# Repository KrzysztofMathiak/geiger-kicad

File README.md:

# geiger-kicad
This repository contains a NODEMCU-ESP32 based geiger counter.
It contains full pcb schematics and code required to run by hosting a web server on the ESP board.

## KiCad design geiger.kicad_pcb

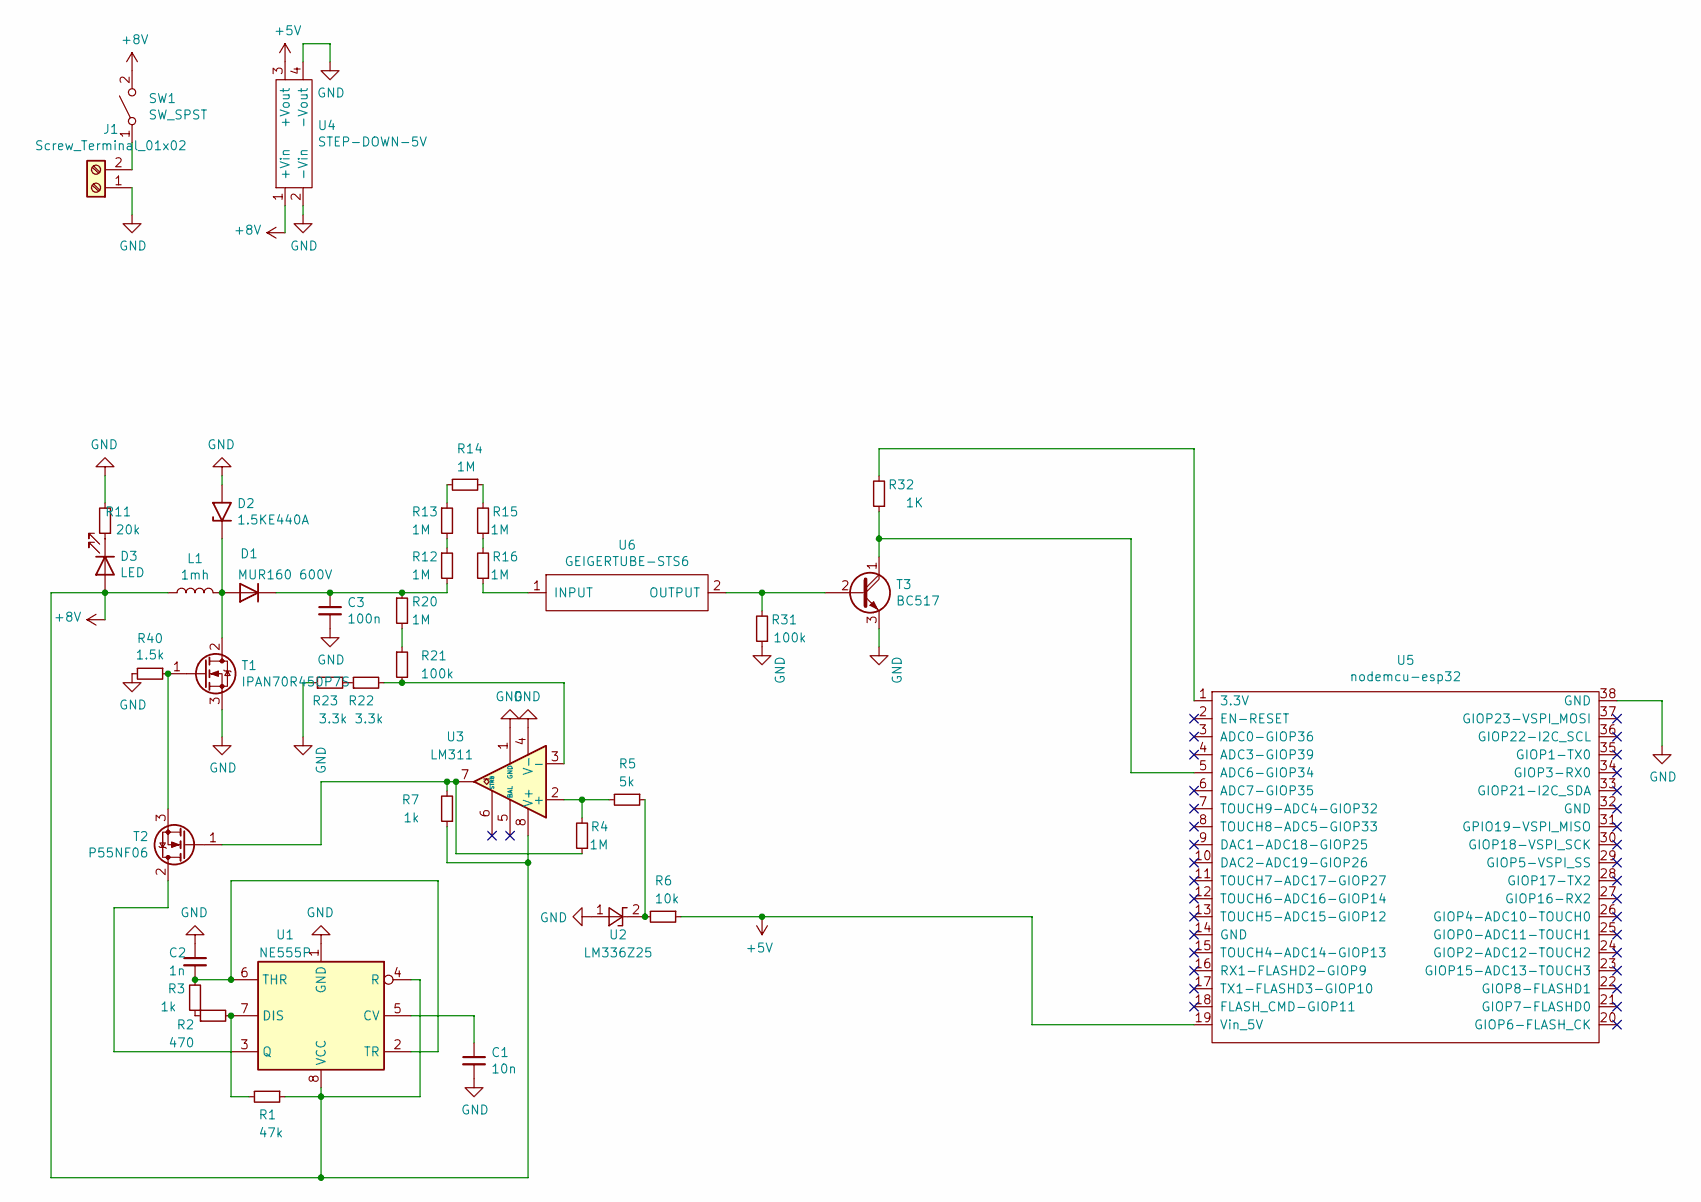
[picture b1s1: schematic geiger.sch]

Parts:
C1: 10n; C_Disc_D3.8mm_W2.6mm_P2.50mm
C2: 1n; C_Disc_D3.8mm_W2.6mm_P2.50mm
C3: 100n; C_Rect_L18.0mm_W5.0mm_P15.00mm_FKS3_FKP3
D1: MUR160 600V; D_DO-35_SOD27_P7.62mm_Horizontal
D2: 1.5KE440A; D_DO-201AE_P15.24mm_Horizontal
D3: LED; LED_D3.0mm
J1: Screw_Terminal_01x02; TerminalBlock_Altech_AK300-2_P5.00mm
L1: 1mh; L_Radial_D8.7mm_P5.00mm_Fastron_07HCP
R1: 47k; R_Axial_DIN0207_L6.3mm_D2.5mm_P7.62mm_Horizontal
R2: 470; R_Axial_DIN0207_L6.3mm_D2.5mm_P7.62mm_Horizontal
R3, R7: 1k; R_Axial_DIN0207_L6.3mm_D2.5mm_P7.62mm_Horizontal
R4, R12, R13, R14, R15, R16, R20: 1M; R_Axial_DIN0207_L6.3mm_D2.5mm_P7.62mm_Horizontal
R5: 5k; R_Axial_DIN0207_L6.3mm_D2.5mm_P7.62mm_Horizontal
R6: 10k; R_Axial_DIN0207_L6.3mm_D2.5mm_P7.62mm_Horizontal
R11: 20k; R_Axial_DIN0207_L6.3mm_D2.5mm_P7.62mm_Horizontal
R21, R31: 100k; R_Axial_DIN0207_L6.3mm_D2.5mm_P7.62mm_Horizontal
R22, R23: 3.3k; R_Axial_DIN0207_L6.3mm_D2.5mm_P7.62mm_Horizontal
R32: 1K; R_Axial_DIN0207_L6.3mm_D2.5mm_P7.62mm_Horizontal
R40: 1.5k; R_Axial_DIN0207_L6.3mm_D2.5mm_P7.62mm_Horizontal
SW1: SW_SPST; PinSocket_1x02_P2.54mm_Vertical
T1: IPAN70R450P7S; TO-247-3_Vertical
T2: P55NF06; TO-220-3_Vertical
T3: BC517; TO-92_Inline
U1: NE555P; DIP-8_W7.62mm
U2: LM336Z25; TO-92_Inline
U3: LM311; DIP-8_W7.62mm
U4: STEP-DOWN-5V; DIP-4_641_ELL
U5: nodemcu-esp32; NODEMCU_ESP32
U6: GEIGERTUBE-STS6; TerminalBlock_Altech_AK300-2_P5.00mm

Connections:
+5V: R6.1, U4.3 (+Vout), U5.19 (Vin_5V)
+8V: D3.2 (A), L1.1, R1.1, R7.1, SW1.2 (B), U1.4 (R), U1.8 (VCC), U3.8 (V+), U4.1 (+Vin)
GND: C1.2, C2.1, C3.2, D2.2 (A2), J1.1, R11.2, R23.1, R31.1, R40.2, T1.3 (S), T3.3 (E), U1.1 (GND), U2.1 (A), U3.1 (GND), U3.4 (V-), U4.2 (-Vin), U4.4 (-Vout), U5.38 (GND)
unnamed: C1.1, U1.5 (CV)
unnamed: C2.2, R3.2, U1.2 (TR), U1.6 (THR)
unnamed: C3.1, D1.1 (K), R12.2, R20.1
unnamed: D1.2 (A), D2.1 (A1), L1.2, T1.2 (D)
unnamed: D3.1 (K), R11.1
unnamed: J1.2, SW1.1 (A)
unnamed: R1.2, R2.2, U1.7 (DIS)
unnamed: R2.1, R3.1
unnamed: R4.1, R7.2, T2.1 (G), U3.7
unnamed: R4.2, R5.2, U3.2 (+)
unnamed: R5.1, R6.2, U2.2 (K)
unnamed: R12.1, R13.2
unnamed: R13.1, R14.2
unnamed: R14.1, R15.2
unnamed: R15.1, R16.2
unnamed: R16.1, U6.1 (INPUT)
unnamed: R20.2, R21.1
unnamed: R21.2, R22.2, U3.3 (-)
unnamed: R22.1, R23.2
unnamed: R31.2, T3.2 (B), U6.2 (OUTPUT)
unnamed: R32.1, T3.1 (C), U5.5 (ADC6-GIOP34)
unnamed: R32.2, U5.1 (3.3V)
unnamed: R40.1, T1.1 (G), T2.3 (S)
unnamed: T2.2 (D), U1.3 (Q)

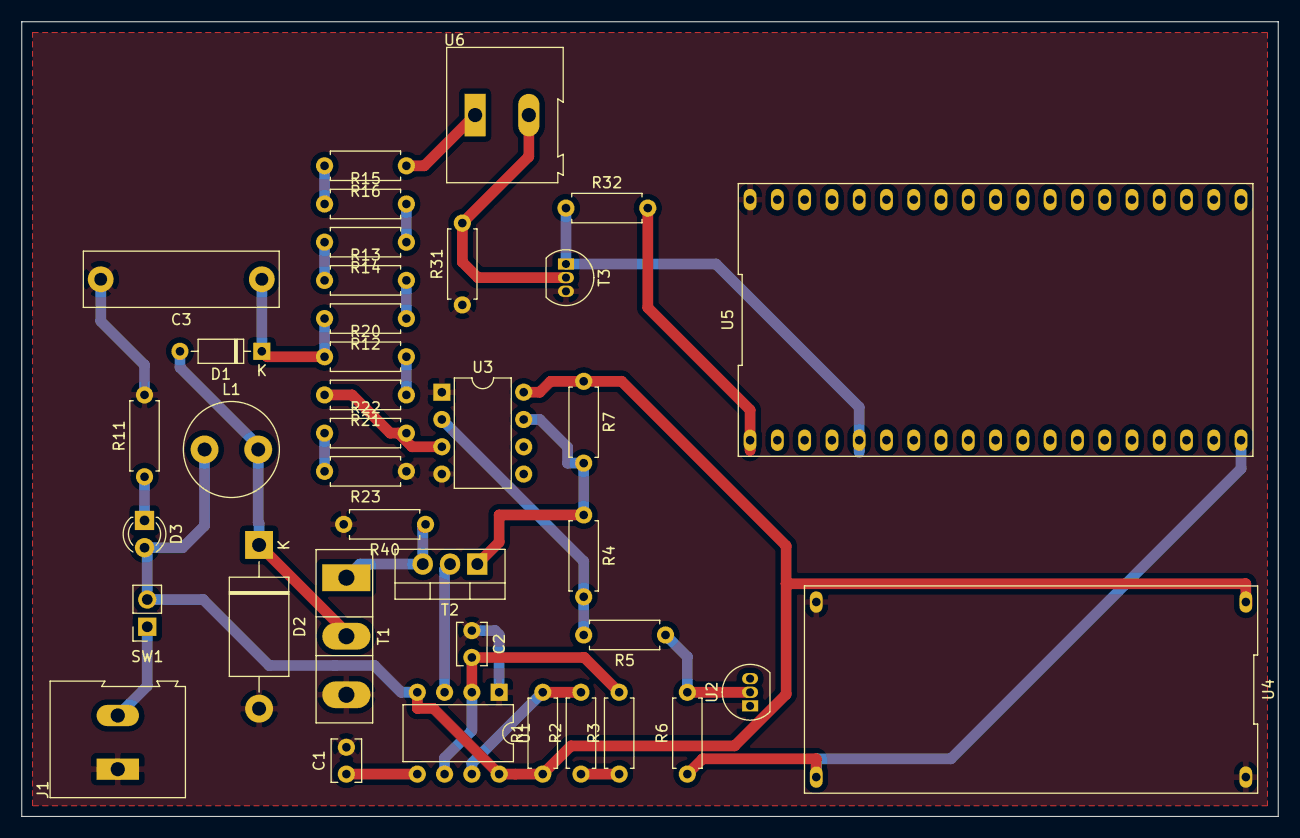
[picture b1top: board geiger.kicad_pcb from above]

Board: 2 copper layers, 117.0 x 74.0 mm, 38 parts (0 on the bottom side), 27 nets.

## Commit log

2021-04-19 Create geigerwifi.ino
    Arduino script
2021-04-20 Clean up
    Cleaned up files and PCB routing.
2021-04-21 Better connectors and minor trace improvements.
2021-04-25 T1 gate fix
2021-04-25 T1 Fix
2021-04-26 Traces and footprint fix
2021-04-28 Miller capacitance discharge fix
2021-05-12 T symbol fixes
2021-05-12 T1 modernized
